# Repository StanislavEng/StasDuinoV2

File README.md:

# StasDuinoV2
I had a bit of time still left in the month to work on PCB design (with Autodesk Eagle).  
As a result I attempted to create another Arduino Clone, this time using the SMD ATMega as well as attempt BT capabilities.

At the time I was looking, I was unable to find a decent (reasonably priced) BT module. 
I found a small ESP module after several hours of looking and I created its part to be used. 
However, this chip, as long with other "reasonably priced" BT chips were actual MCUs in the first place,  
it began to feel a bit redundant like using an MCU as a serial converter for programming (heh). 

Additionally, I was not too sure how to properly create communication between the Arduino and the BT.
My idea later (that I had not yet implemented) was hooking up the two via RX/TX lines (which make sense to me)  
and then using MOSFETs to block communication into the ESP while programming the Arduino. 

Otherwise, I changed the serial programmer to an FTDI chip, and instead looked at and referenced other Arduino clone  
datasheets including the Sparkfun RedBoard to see other ways of programming, which was interesting in its own way. 

Overall, after this I want to make one more "Arduino Clone", instead using a SAMD21, finally adding in the BT,  
and lastly using Altium (Student version) to replace Eagle and be more industry relatable. 

I made almost everything myself. I ended up getting lazy and impatient again and imported the push button (I think)  
and the... things for the pinouts. 

Was fun, still took about two revisions for a trace out I was happy with.

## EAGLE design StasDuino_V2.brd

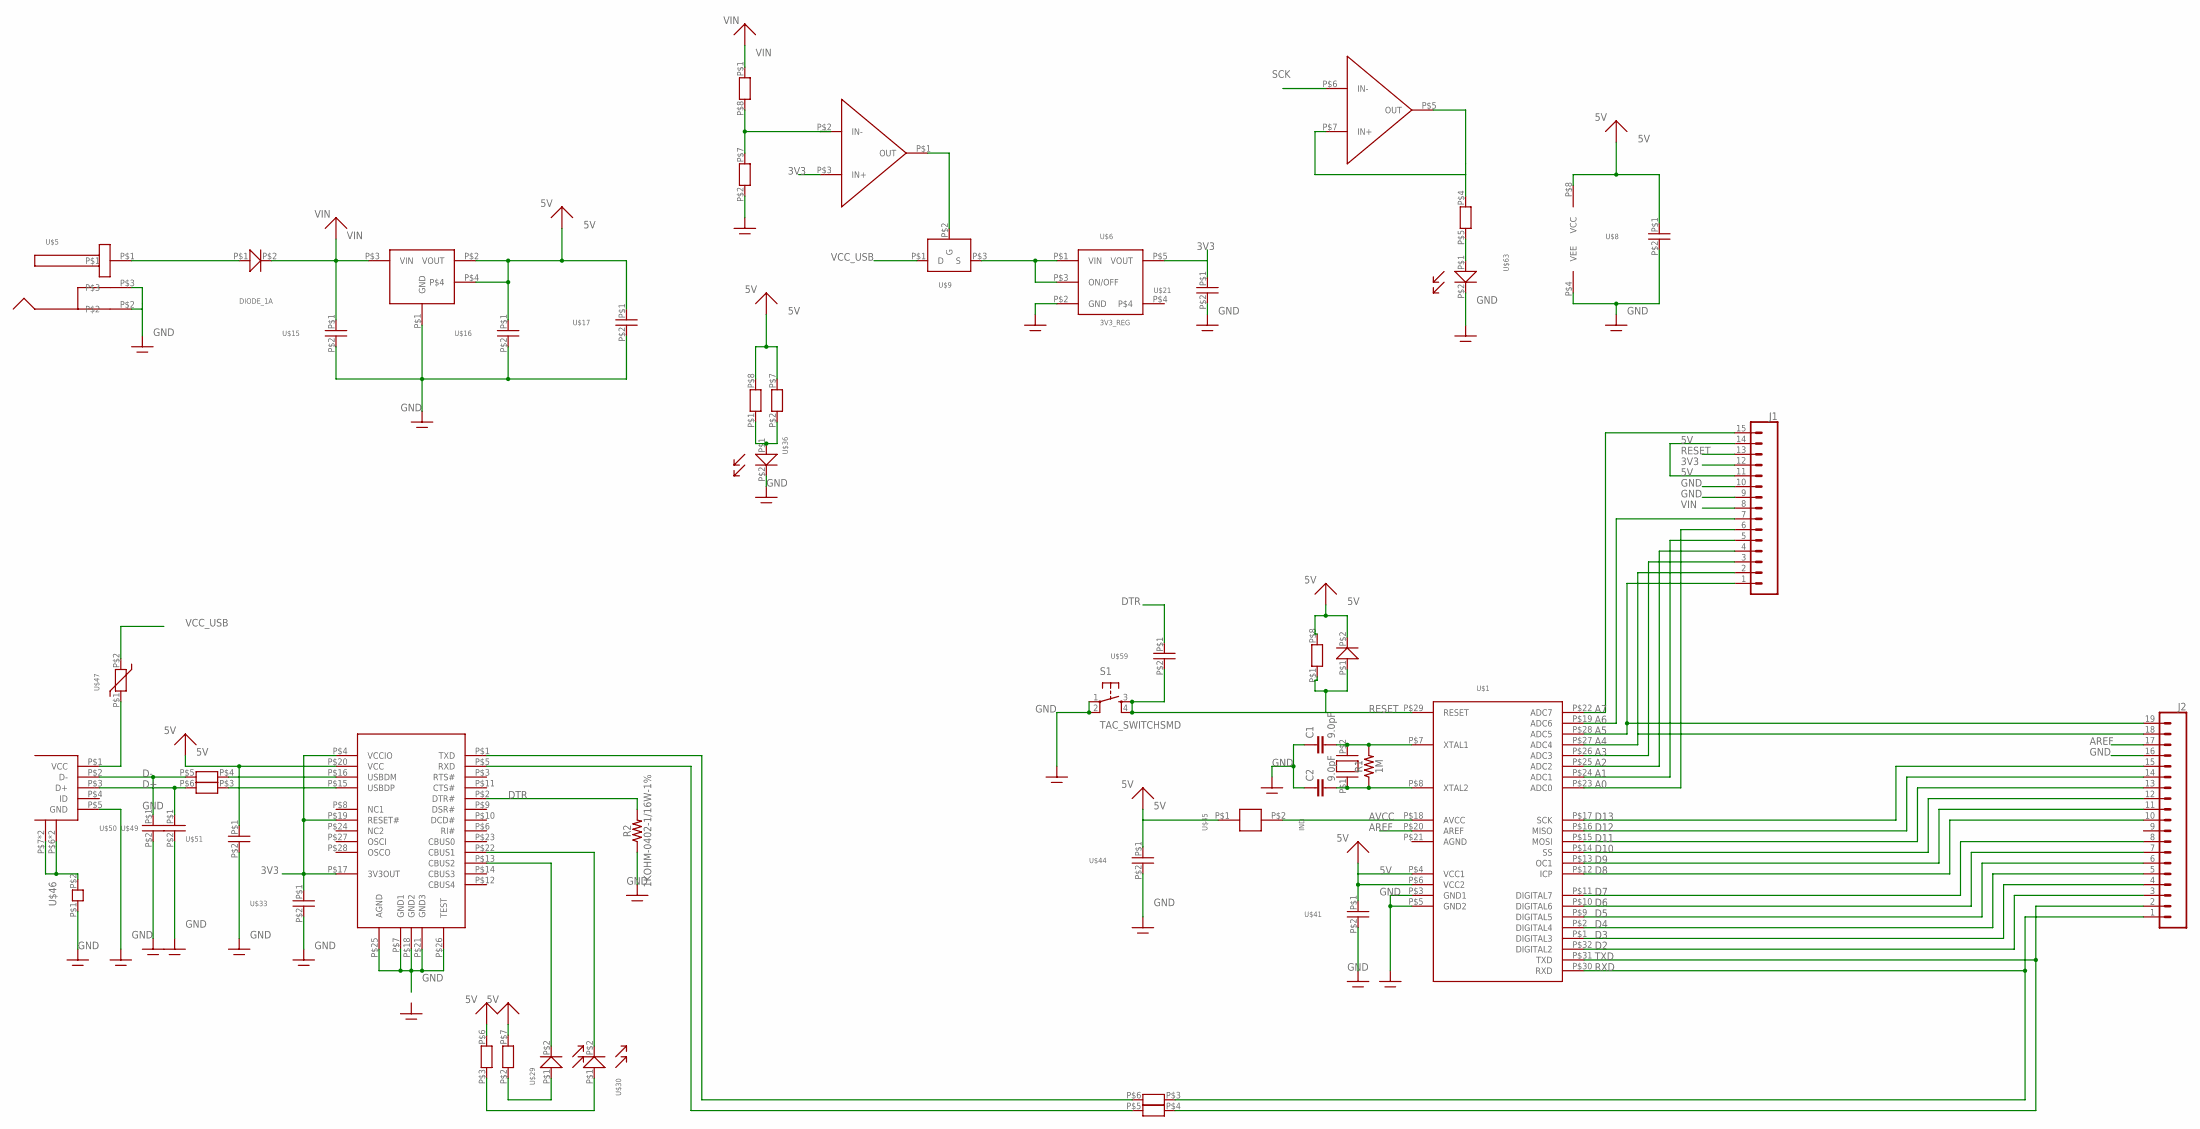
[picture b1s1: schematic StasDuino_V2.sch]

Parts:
C1, C2: 9.0pF; 0603
J1: CONN_15; 1X15
J2: CONN_19; 1X19
R1: 1M; 0603
R2: 1KOHM-0402-1/16W-1%; 0402
S1: TAC_SWITCHSMD; TACTILE-SWITCH-SMD
U$1: ATMEGA328P_TQFP
U$2: FTDI_SERIAL
U$3: USB_MICRO
U$4: 5V_REG
U$5: DC_POWERJACK
U$6: 3V3_REG
U$7: OPAMP
U$8, U$15, U$16, U$17, U$21, U$33, U$41, U$44, U$49, U$50, U$51, U$59: CAP_0805
U$9: PMOS
U$12: DIODE_1A
U$20, U$34, U$48: RES_ARRAY
U$29, U$30, U$36, U$63: LED_0805
U$45: IND
U$46: FERRITE_BEAD
U$47: RESET_FUSE
U$57: CRYSTAL
U$60: DIODE

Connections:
3V3: J1.12, U$2.P$4 (VCCIO), U$2.P$17 (3V3OUT), U$2.P$19 (RESET#), U$6.P$5 (VOUT), U$7.P$3 (IN+), U$21.P$1, U$33.P$1
5V: J1.11, J1.14, U$1.P$4 (VCC1), U$1.P$6 (VCC2), U$2.P$20 (VCC), U$4.P$2 (VOUT), U$4.P$4, U$7.P$8 (VCC), U$8.P$1, U$16.P$1, U$17.P$1, U$34.P$7, U$34.P$8, U$41.P$1, U$44.P$1, U$45.P$1, U$48.P$6, U$48.P$7, U$48.P$8, U$51.P$1, U$60.P$2
A0: J1.6, U$1.P$23 (ADC0)
A1: J1.5, U$1.P$24 (ADC1)
A2: J1.4, U$1.P$25 (ADC2)
A3: J1.3, U$1.P$26 (ADC3)
A4: J1.2, J2.18, U$1.P$27 (ADC4)
A5: J1.1, J2.19, U$1.P$28 (ADC5)
A6: J1.7, U$1.P$19 (ADC6)
A7: J1.15, U$1.P$22 (ADC7)
AREF: J2.17, U$1.P$20 (AREF)
AVCC: U$1.P$18 (AVCC), U$45.P$2
D2: J2.3, U$1.P$32 (DIGITAL2)
D3: J2.4, U$1.P$1 (DIGITAL3)
D4: J2.5, U$1.P$2 (DIGITAL4)
D5: J2.6, U$1.P$9 (DIGITAL5)
D6: J2.7, U$1.P$10 (DIGITAL6)
D7: J2.8, U$1.P$11 (DIGITAL7)
D8: J2.10, U$1.P$12 (ICP)
D9: J2.11, U$1.P$13 (OC1)
D10: J2.12, U$1.P$14 (SS)
D11: J2.13, U$1.P$15 (MOSI)
D12: J2.14, U$1.P$16 (MISO)
D13: J2.15, U$1.P$17 (SCK)
D+: U$3.P$3 (D+), U$20.P$6, U$49.P$1
D-: U$3.P$2 (D-), U$20.P$5, U$50.P$1
DTR: R2.2, U$2.P$2 (DTR#), U$59.P$1
GND: C1.1, C2.1, J1.9, J1.10, J2.16, R2.1, S1.1, S1.2, U$1.P$3 (GND1), U$1.P$5 (GND2), U$2.P$7 (GND1), U$2.P$18 (GND2), U$2.P$21 (GND3), U$2.P$25 (AGND), U$2.P$26 (TEST), U$3.P$5 (GND), U$4.P$1 (GND), U$5.P$2, U$5.P$3, U$6.P$2 (GND), U$7.P$4 (VEE), U$8.P$2, U$15.P$2, U$16.P$2, U$17.P$2, U$20.P$2, U$21.P$2, U$33.P$2, U$36.P$2, U$41.P$2, U$44.P$2, U$46.P$1, U$49.P$2, U$50.P$2, U$51.P$2, U$63.P$2
unnamed: C1.2, R1.2, U$1.P$7 (XTAL1), U$57.P$2
unnamed: U$5.P$1, U$12.P$1
unnamed: U$3.P$6 (SHIELD1), U$3.P$7 (SHIELD2), U$3.P$8 (SHIELD1), U$3.P$9 (SHIELD2), U$46.P$2
unnamed: C2.2, R1.1, U$1.P$8 (XTAL2), U$57.P$1
unnamed: U$7.P$2 (IN-), U$20.P$7, U$20.P$8
unnamed: U$7.P$1 (OUT), U$9.P$2 (G)
unnamed: U$29.P$1, U$48.P$2
unnamed: U$6.P$1 (VIN), U$6.P$3 (ON/OFF), U$9.P$3 (S)
unnamed: U$30.P$1, U$48.P$3
unnamed: U$48.P$5, U$63.P$1
unnamed: U$2.P$15 (USBDP), U$20.P$3
unnamed: U$2.P$5 (RXD), U$34.P$5
unnamed: U$2.P$1 (TXD), U$34.P$6
unnamed: U$2.P$22 (CBUS1), U$30.P$2
unnamed: U$2.P$16 (USBDM), U$20.P$4
unnamed: U$2.P$13 (CBUS2), U$29.P$2
unnamed: U$34.P$1, U$34.P$2, U$36.P$1
unnamed: U$3.P$1 (VCC), U$47.P$1
unnamed: U$7.P$5 (OUT), U$7.P$7 (IN+), U$48.P$4
RESET: J1.13, S1.3, S1.4, U$1.P$29 (RESET), U$48.P$1, U$59.P$2, U$60.P$1
RXD: J2.1, U$1.P$30 (RXD), U$34.P$3
SCK: U$7.P$6 (IN-)
TXD: J2.2, U$1.P$31 (TXD), U$34.P$4
VCC_USB: U$9.P$1 (D), U$47.P$2
VIN: J1.8, U$4.P$3 (VIN), U$12.P$2, U$15.P$1, U$20.P$1

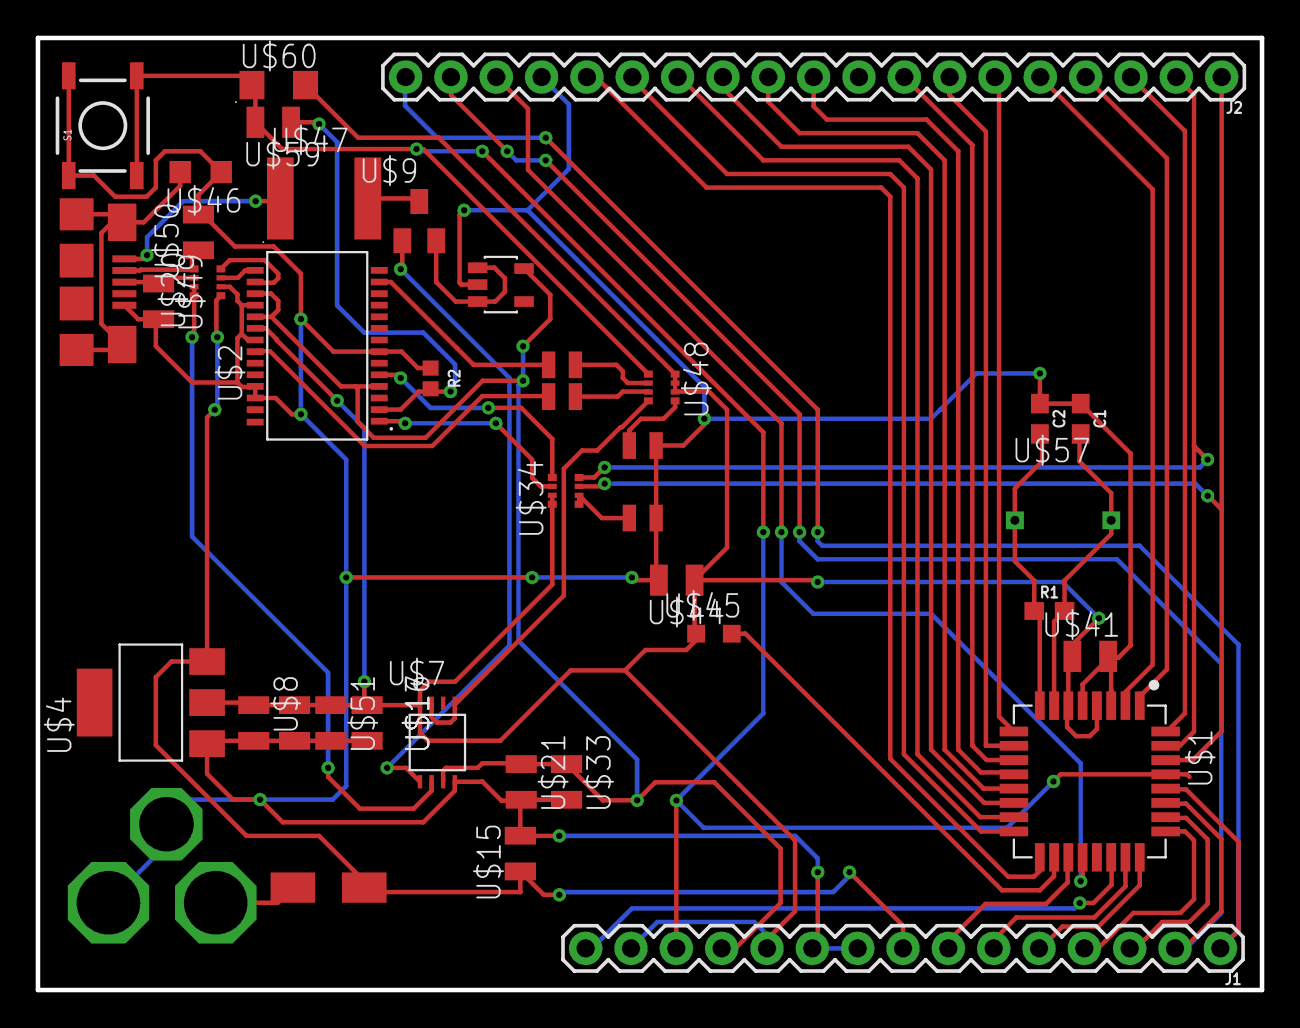
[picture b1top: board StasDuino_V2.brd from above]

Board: 2 copper layers, 68.6 x 53.3 mm, 40 parts (0 on the bottom side), 52 nets.

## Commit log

2021-04-01 Completed Schematic
2021-04-01 Adding in libraries too
2021-04-02 Finished Revision One. Not the best tracing but a good baseline
